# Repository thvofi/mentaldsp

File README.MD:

<picture>
  <source
    media="(prefers-color-scheme: dark)"
    srcset="./docs/assets/mental-dark.png"
  >
  <source
    media="(prefers-color-scheme: light)"
    srcset="./docs/assets/mental-light.png"
  >
  
</picture>

<br clear="left" />

### Table of Contents

- [Bill of Materials](#bill-of-materials)
- [Hardware](#hardware)
- [Software](#software)
- [Acknowledgment](#acknowledgment)

## Bill of Materials

|Component|Specifications|Quantity|Price (per unit)|Price (total)|Where to buy|
|---|---|---|---|---|---|
|Stepper Motor|NEMA 17 (17HS4023)|3|€6.53|€19.59|[AliExpress](https://a.aliexpress.com/_EuMzXUE)|
|Stepper Motor Driver|TMC2209 (BTT v1.3)|3|€3.8|€11.4|[AliExpress](https://a.aliexpress.com/_EGuPfX0)|
|Flexible shaft|L300mm D4mm|3|€5.93|€17.79|[AliExpress](https://a.aliexpress.com/_EHIs5H8)|
|Coupler (motor to shaft)|5mm to 4mm|3|€0.45|€1.35|[AliExpress](https://a.aliexpress.com/_EwQRNfs)|
|Coupler (shaft to pots)|5mm to 6.35mm|3|€0.45|€1.35|[AliExpress](https://a.aliexpress.com/_EwQRNfs)|
|2020 Aluminum Extrusion|L100mm|6|€depends|€depends||
|2040 Aluminum Extrusion|L100mm|3|€depends|€depends||
|2020 Extrusion Bracket|90deg|6|€0.25|€1.5|[AliExpress](https://a.aliexpress.com/_EIpKqK2)|
|Slide-in Nut|M5 10mm|48|€0.16|€7.68|[AliExpress](https://a.aliexpress.com/_EICuedC)|
|DIN912 M5 screws|M5 10mm|18|€0.19|€3.42|[AliExpress](https://a.aliexpress.com/_EJXdA0I)|
|ISO7380 M5 screws|M5 10mm|30|€0.16|€4.8|[AliExpress](https://a.aliexpress.com/_EGQIF4S)|
|M5 washers (for 10mm M5 screws)|M5|48|€depends|€depends||
|3M/Scotch Dual lock|1m|1|€depends|€depends||
|ESP32-S3 Dev Board|Supermini|1|€3.8|€3.8|[AliExpress](https://a.aliexpress.com/_EJnZ8Py)|

## Hardware

### KiCAD

rendered with [kicad-render](https://github.com/linalinn/kicad-render)

### 3D models

## Software

### Embedded

### Recording and Training

## Acknowledgment

This project would not exist without the help of these amazing people and projects:
- My advisor and good friend [Valtteri](https://kallinen.xyz/)
- Solomon at the [Aalto Fablab](https://studios.aalto.fi/fablab/)
- [Daniel Frenkel](https://valarsystems.com/) and his [Trinamic Guide](https://valarsystems.com/products/controlling-trinamic-drivers-pdf)
- teemuatlut for making the [TMCStepper](https://github.com/teemuatlut/TMCStepper) library
- [DukeDesigns3D](https://dukedesigns3d.com/) and [JHS Pedals](https://www.youtube.com/@jhspedals) for the inspiration from the [Toe-N Control](https://www.youtube.com/watch?v=elcASapCZRY)

Projects I have looked at:
- [AndreaFavero71/stepper_sensorless_homing](https://github.com/AndreaFavero71/stepper_sensorless_homing)
- [janelia-arduino/TMC2209](https://github.com/janelia-arduino/TMC2209)

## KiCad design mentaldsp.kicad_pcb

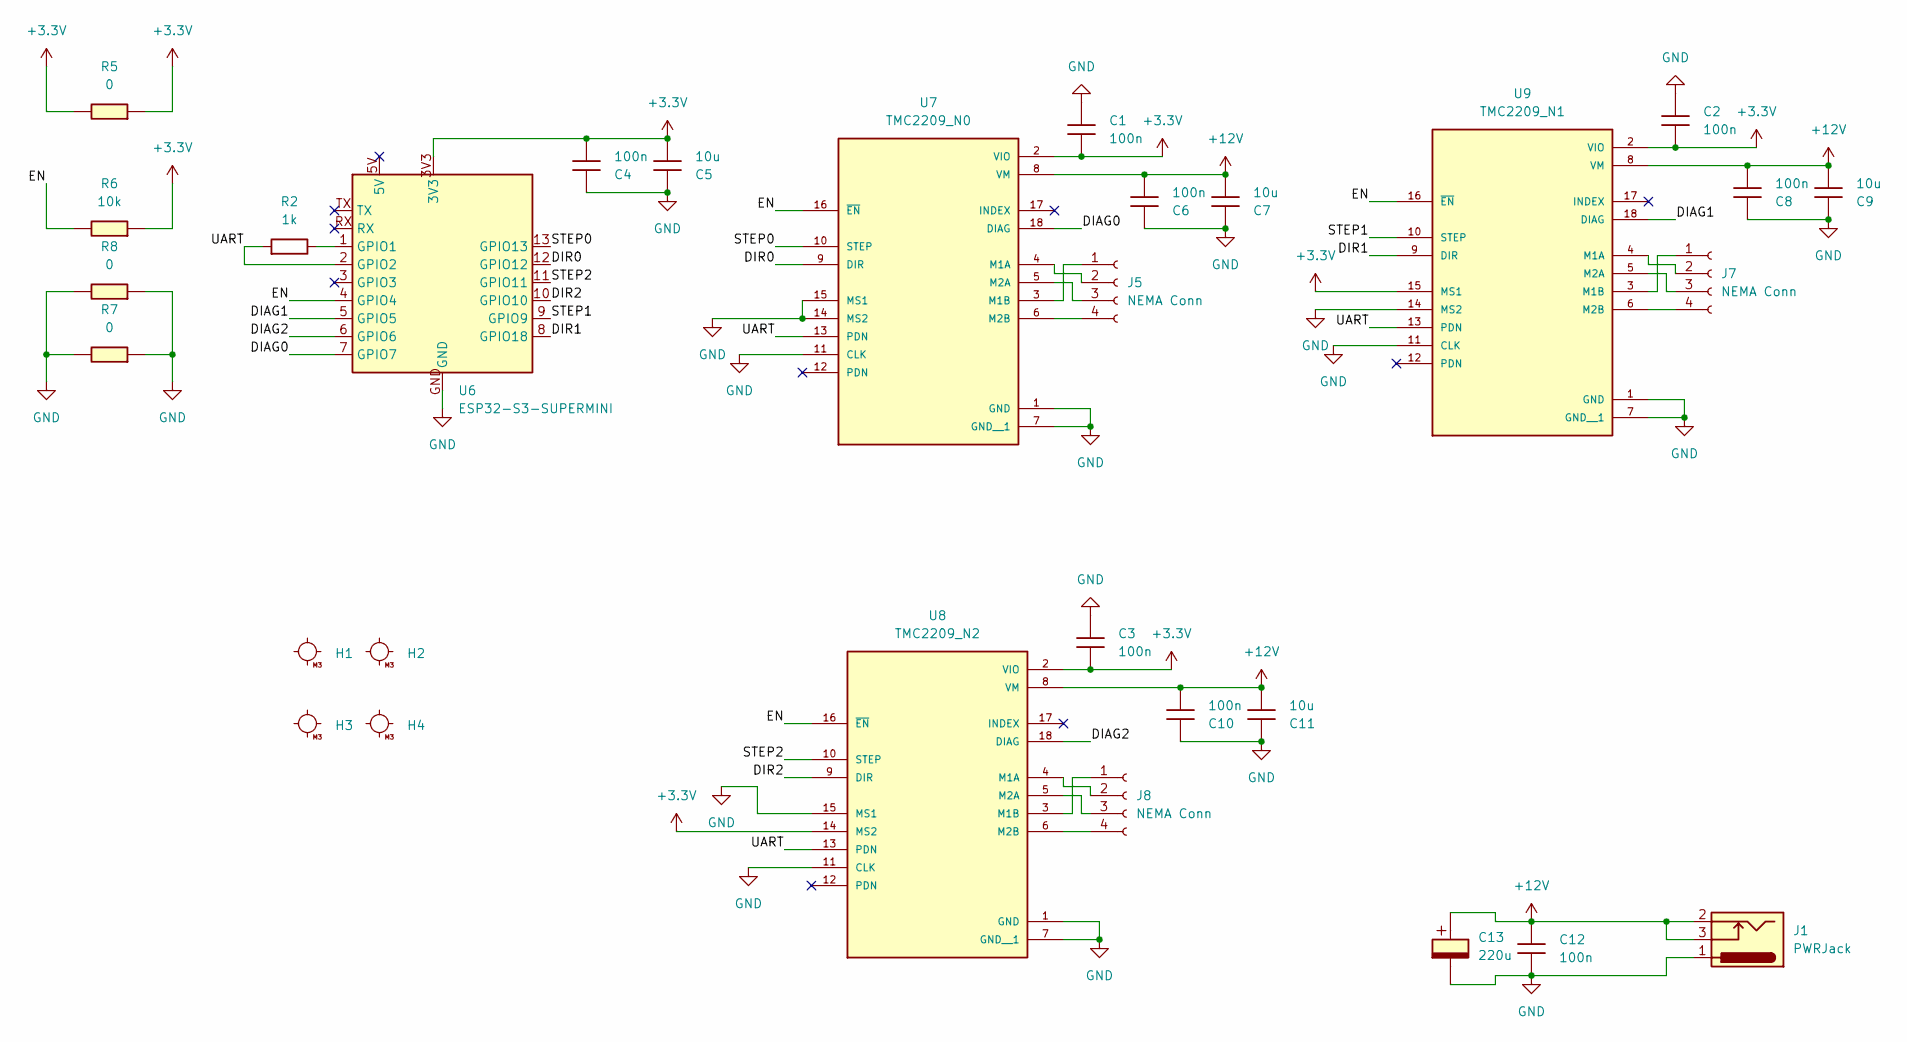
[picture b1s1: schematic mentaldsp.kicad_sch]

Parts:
C1, C2, C3, C4, C6, C8, C10, C12: 100n; C_1206_3216Metric
C5, C7, C9, C11: 10u; C_1206_3216Metric
C13: 220u; CP_Elec_100uF_Panasonic_EEE-FN1E101UL
H1, H2, H3, H4: MountingHole_M3
J1: PWRJack; CUIDevices_PJ-002AH-SMT-TR_PWRJack_2x5.5mm
J5, J7, J8: NEMA Conn; PinHeader_1x04_P2.54mm_Vertical
R2: 1k; R_1206_3216Metric
R5, R7, R8: 0; R_1206_3216Metric
R6: 10k; R_1206_3216Metric
U6: ESP32-S3-SUPERMINI; ESP32-S3-SuperMini
U7: TMC2209_N0; BTT_TMC2209; PARTREV 1.20
U8: TMC2209_N2; BTT_TMC2209; PARTREV 1.20
U9: TMC2209_N1; BTT_TMC2209; PARTREV 1.20

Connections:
+3.3V: C1.2, C2.2, C3.2, C4.2, C5.2, R5.1, R5.2, R6.2, U6.3V3, U7.2 (VIO), U8.2 (VIO), U8.14 (MS2), U9.2 (VIO), U9.15 (MS1)
+12V: C6.2, C7.2, C8.2, C9.2, C10.2, C11.2, C12.1, C13.1, J1.2, J1.3, U7.8 (VM), U8.8 (VM), U9.8 (VM)
/DIAG0: U6.7 (GPIO7), U7.18 (DIAG)
/DIAG1: U6.5 (GPIO5), U9.18 (DIAG)
/DIAG2: U6.6 (GPIO6), U8.18 (DIAG)
/DIR0: U6.12 (GPIO12), U7.9 (DIR)
/DIR1: U6.8 (GPIO18), U9.9 (DIR)
/DIR2: U6.10 (GPIO10), U8.9 (DIR)
/EN: R6.1, U6.4 (GPIO4), U7.16 (~EN), U8.16 (~EN), U9.16 (~EN)
/STEP0: U6.13 (GPIO13), U7.10 (STEP)
/STEP1: U6.9 (GPIO9), U9.10 (STEP)
/STEP2: U6.11 (GPIO11), U8.10 (STEP)
/UART: R2.2, U6.2 (GPIO2), U7.13 (PDN), U8.13 (PDN), U9.13 (PDN)
GND: C1.1, C2.1, C3.1, C4.1, C5.1, C6.1, C7.1, C8.1, C9.1, C10.1, C11.1, C12.2, C13.2, J1.1, R7.1, R7.2, R8.1, R8.2, U6.GND, U7.1 (GND), U7.7 (GND__1), U7.11 (CLK), U7.14 (MS2), U7.15 (MS1), U8.1 (GND), U8.7 (GND__1), U8.11 (CLK), U8.15 (MS1), U9.1 (GND), U9.7 (GND__1), U9.11 (CLK), U9.14 (MS2)
unnamed: J5.1, U7.3 (M1B)
unnamed: J5.2, U7.4 (M1A)
unnamed: J5.3, U7.5 (M2A)
unnamed: J5.4, U7.6 (M2B)
unnamed: J7.1, U9.3 (M1B)
unnamed: J7.2, U9.4 (M1A)
unnamed: J7.3, U9.5 (M2A)
unnamed: J7.4, U9.6 (M2B)
unnamed: J8.1, U8.3 (M1B)
unnamed: J8.2, U8.4 (M1A)
unnamed: J8.3, U8.5 (M2A)
unnamed: J8.4, U8.6 (M2B)
unnamed: R2.1, U6.1 (GPIO1)

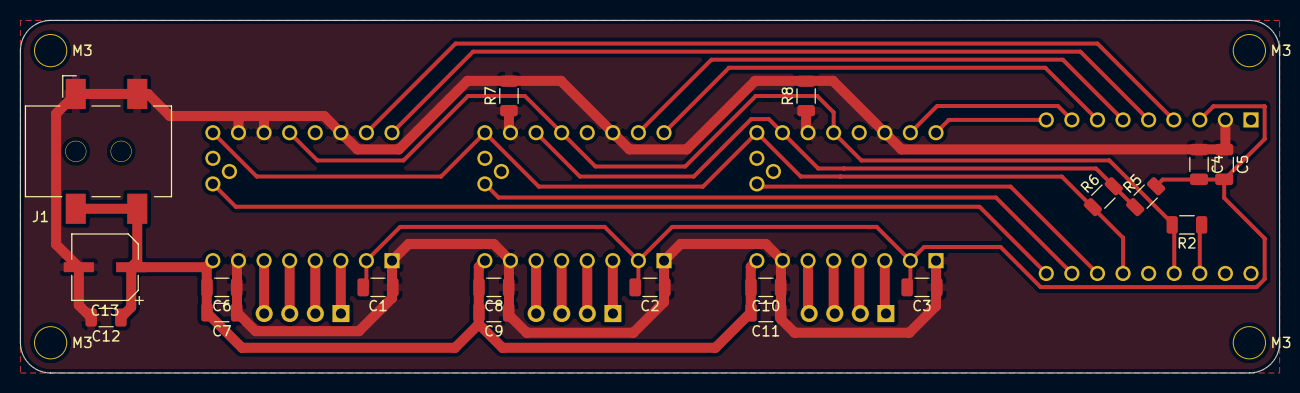
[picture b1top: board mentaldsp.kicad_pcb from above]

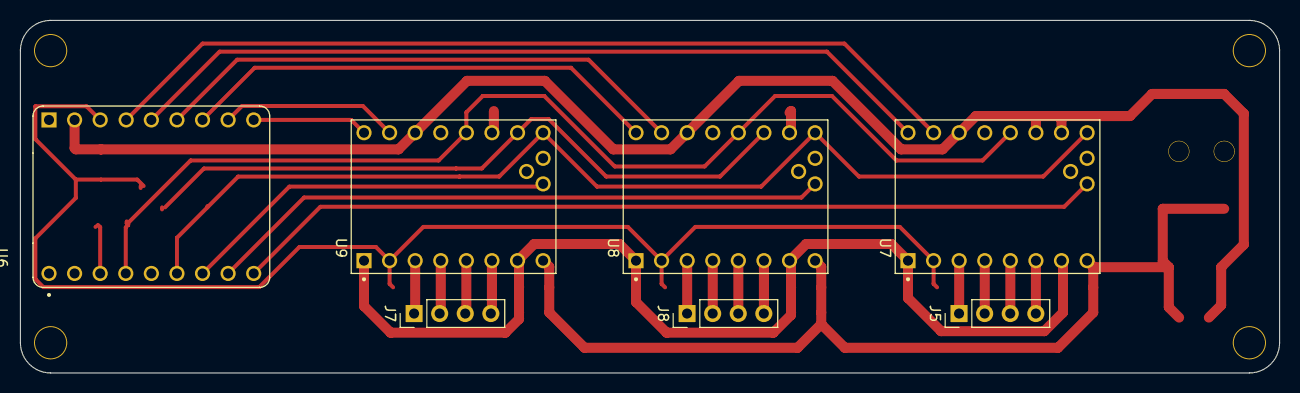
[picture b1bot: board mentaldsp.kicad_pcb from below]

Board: 2 copper layers, 125.0 x 35.0 mm, 30 parts (7 on the bottom side), 27 nets.

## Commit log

2026-03-17 pre-library
2026-03-17 add library as submodule
2026-03-18 basic routing
2026-03-18 v0.0.1 including power
2026-03-18 add uart via 1mm hole
2026-03-24 add frame joint
2026-04-20 nema17 extrusion mount
2026-04-22 readme
2026-04-22 update LICENSE
2026-05-06 update BOM
2026-05-28 v2 with BTT TMC2209
2026-05-28 decoupling
2026-05-28 cleanup
2026-05-28 cleanup2
2026-05-28 gerber
2026-05-28 resize
2026-05-28 replace to SMD jack
2026-05-28 fix polarity
2026-06-03 housekeeping
